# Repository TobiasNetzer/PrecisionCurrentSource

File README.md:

## A precision current source that can be configured for currents up to ~10mA.

I needed to verify the current measurement accuracy of the low-current ranges of my data logger and a reference for calibration purposes. Since I don’t own a programmable current source like a Keithley 220 or SMU, I came up with this approach instead. Check [here](https://tobiasnetzer.github.io/posts/current-source/) for more info.

Documentation
- [Schematic](https://github.com/TobiasNetzer/PrecisionCurrentSource/blob/main/Documentation/Schematic.pdf)
- [Assembly Drawing](https://github.com/TobiasNetzer/PrecisionCurrentSource/blob/main/Documentation/Assembly%20Drawing.pdf)
- [BOM](https://htmlpreview.github.io/?https://github.com/TobiasNetzer/PrecisionCurrentSource/blob/main/Documentation/BOM.html)

---

## Limitations of the Design

Due to the high internal resistance of CR2032 coin cells, they are unable to deliver currents higher than approximately 15mA. This inherently limits the maximum output of the constant current source. However, it's not the only limiting factor. The op-amp used in the circuit can only sink up to 15mA, making the current source only suitable for output currents up to around 10mA.  

In addition, the voltage swing across the load is limited to 1.4V. For example, at a current of 1mA, the maximum  load is limited to 1.4kΩ. This further restricts the usable range of the current source.

These limitations should be taken into account when using this current source!

## First Tests

The design has not been fully tested yet! The output current has been measured to be within ±0.2%.

| Configured Current &nbsp; &nbsp; &nbsp; &nbsp; &nbsp; &nbsp;          | Measured Current &nbsp; &nbsp; &nbsp; &nbsp; &nbsp; &nbsp;        | Error &nbsp; &nbsp; &nbsp; &nbsp; &nbsp; &nbsp;           |
| ---                                                                   | ---                                                               | ---                                                       |
| 100nA                                                                 | 99.82nA                                                           | -0.18%                                                    |
| 1µA                                                                   | 0.999µA                                                           | -0.1%                                                     |
| 100µA                                                                 | 100.07µA                                                          | 0.07%                                                     |
| 1mA                                                                   | 0.999mA                                                           | -0.1%                                                     |

Several other aspects such as load regulation, temperature stability and ripple/noise should also be tested. However, I currently lack the equipment to accurately perform these tests.

I did sample the output current with my datalogger at 1kHz to get an idea of how noisy the current source is. These results should be taken with a grain of salt, since the logger’s ADC does some internal averaging and I don't have a known reference to test the logger against.

| Current Source &nbsp; &nbsp; &nbsp; &nbsp; &nbsp; &nbsp;          | Peak-Peak Current &nbsp; &nbsp; &nbsp; &nbsp; &nbsp; &nbsp;     |
| ---                                                               | ---                                                             |
| 1µA                                                               | 1.23nA                                                          |
| 100µA                                                             | 73.25nA                                                         |
| 1mA                                                               | 1.24µA                                                          |

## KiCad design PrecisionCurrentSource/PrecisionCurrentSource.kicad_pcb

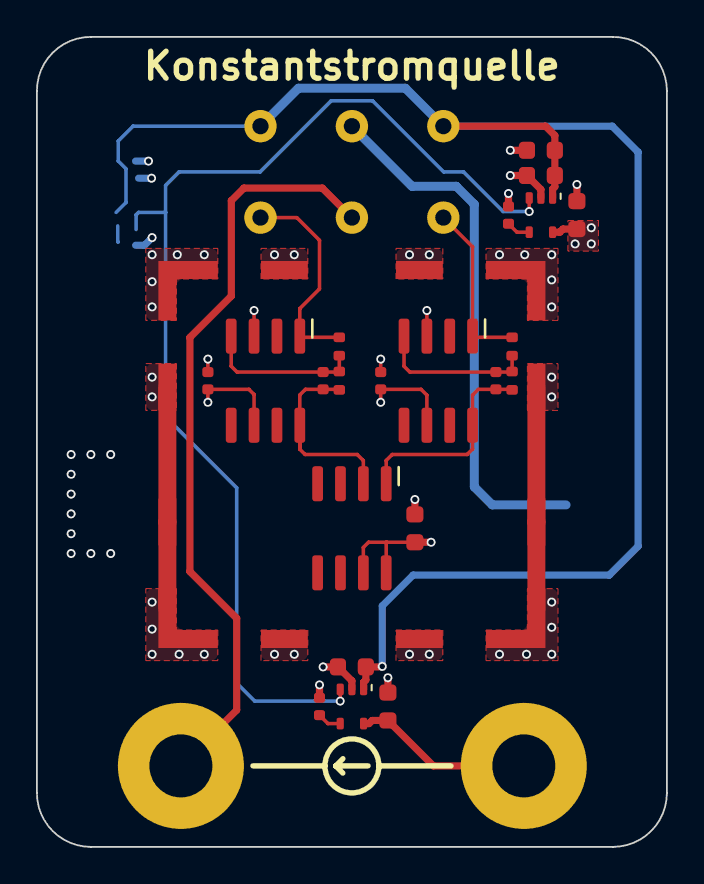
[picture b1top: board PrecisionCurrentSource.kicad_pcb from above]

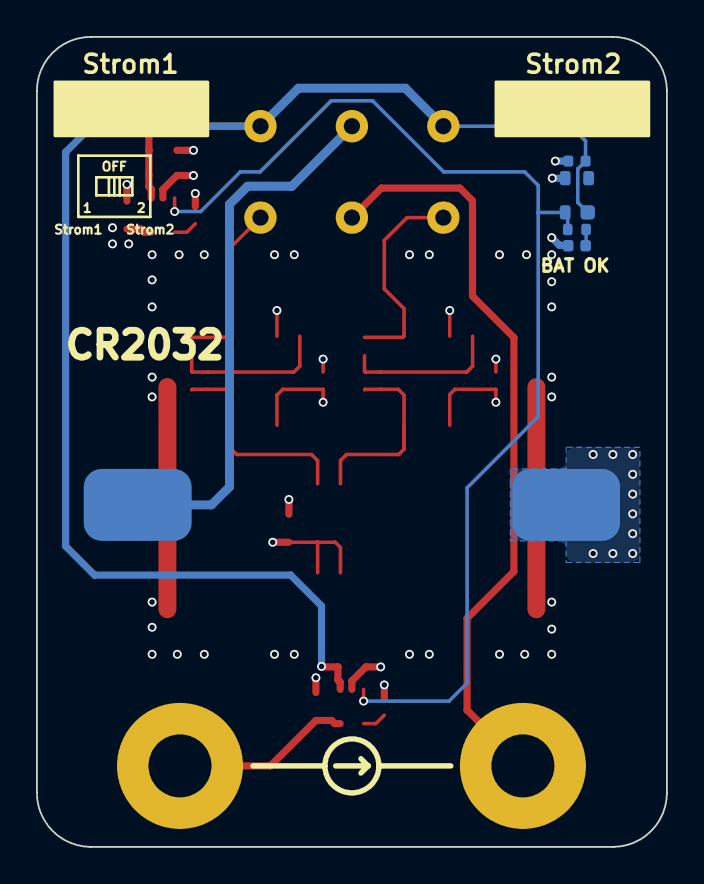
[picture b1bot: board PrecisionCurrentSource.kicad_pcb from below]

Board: 4 copper layers, 35.0 x 45.0 mm, 30 parts (6 on the bottom side), 16 nets.

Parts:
BT1: 2x CR2032; Keystone_1062
C1, C13: 10µF; Capacitor_0603
C2, C3, C5: 100nF; Capacitor_0402
C4, C6, C8, C11: 10nF; Capacitor_0402
C7, C9, C10, C12: 1µF; Capacitor_0603
D1: Green; LED_0402
H1, H2: MountingHole
J1: EMI-Shield; Wuerth_36103205_20x20mm
R1: 8k2; Resistor_0402
R2, R4: 1k 0,05%; Resistor_0402
R3: 1M 0,1%; Resistor_0402
R5: 100k 0,05%; Resistor_0402
SW1: 600DP3S2M4R
U1: BU4947F; SOP4
U2, U3: LMP7721; SOIC-8
U4: REF200AU; SOIC-8
U5: TPS71745; SC70-5
U6: TPS71715; SC70-5

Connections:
+1V5: C12.1, H1.1, U6.5 (OUT)
+4V5: C3.1, C5.1, C9.1, C13.1, U2.6 (V+), U3.6 (V+), U4.7, U4.8, U5.5 (OUT)
+BATT: C1.1, C2.1, C7.1, C10.1, SW1.4 (A), SW1.6 (C), U1.2 (VDD), U5.1 (IN), U6.1 (IN)
/PWR_EN: R1.1, U1.1 (VOUT), U5.3 (EN), U6.3 (EN)
GND: BT1.2 (-), C1.2, C2.2, C3.2, C5.2, C7.2, C8.2, C9.2, C10.2, C11.2, C12.2, C13.2, D1.1 (K), J1.1 (Shield), U1.4 (GND), U2.3 (V-), U3.3 (V-), U5.2 (GND), U6.2 (GND)
unnamed: BT1.1 (+), SW1.5 (B)
unnamed: C4.2, R2.2, R3.2, U2.4
unnamed: C6.2, R4.2, R5.2, U3.4
unnamed: D1.2 (A), R1.2
unnamed: R3.1, SW1.1 (A), U2.1 (+)
unnamed: H2.1, SW1.2 (B)
unnamed: R5.1, SW1.3 (C), U3.1 (+)
unnamed: C4.1, R2.1, U2.8 (-), U4.1
unnamed: C6.1, R4.1, U3.8 (-), U4.2
unnamed: C8.1, U5.4 (NR)
unnamed: C11.1, U6.4 (NR)

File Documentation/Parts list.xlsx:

Position | Menge | Reference(s) | Wert/Typ | Beschreibung | Hersteller | Hersteller-Nr. | Lieferant | Lieferant-Nr. | Stückpreis | Gesamtpreis
1 | 1 | BT1 | 2x CR2032 | Coin Cell Battery Holders 2X20MM SMT COIN HOLDER | Keystone Electronics | 1062 | Mouser | 534-1062 | 3.02 | 3.02
2 | 2 | C1, C13 | 10µF | 10µF-20%-0603-X5R-10V | Kemet | C0603C106M8PACTU | Mouser | 80-C0603C106M8PACTU | 0.43 | 0.86
3 | 3 | C2, C3, C5 | 100nF | 100nF-20%-0402-X7R-25V | Kemet | C0402C104M3RACTU | Mouser | 80-C0402C104M3R | 0.26 | 0.78
4 | 4 | C4, C6, C8, C11 | 10nF | 10nF-10%-0402-X7R-50V | Kemet | C0402C103K5REC7411 | Mouser | 80-C0402C103K5RECLR | 0.1 | 0.4
5 | 4 | C7, C9, C10, C12 | 1µF | 1µF-10%-0603-X7R-25V | Kemet | C0603C105K3RACTU | Mouser | 80-C0603C105K3R | 0.26 | 1.04
6 | 1 | D1 | Green | LED Green 0402 | Kingbright | APHHS1005ZGC | Mouser | 604-APHHS1005ZGC | 0.66 | 0.66
7 | 1 | J1 | EMI-Shield | EMI Gaskets, Sheets, Absorbers & Shielding WE-SHC SMD Frame 21x21mm | Würth Elektronik | 36103205 | Mouser | 710-36103205 | 2.9 | 2.9
8 | 1 | R1 | 8k2 | 8k2-1%-0402-62.5mW-100ppm | Yageo | AC0402FR-138K2L | Mouser | 603-AC0402FR-138K2L | 0.09 | 0.09
9 | 2 | R2, R4 | 1k 0,05% | 1k-0.05%-0402-62.5mW-5ppm | Susumu | RG1005V-102-W-T1 | Mouser | 754-RG1005V-102-WT1 | 3.12 | 6.24
10 | 1 | R3 | 1M 0,1% | 1M-0.1%-0402-100mW-25ppm | Vishay | MCS0402MD1004BE000 | Mouser | 594-MCS0402MD1004BE0 | 0.66 | 0.66
11 | 1 | R5 | 100k 0,05% | 100k-0.05%-0402-62.5mW-10ppm | Vishay | TNPU0402100KAYEP00 | Mouser | 71-TNPU0402100KAYEP0 | 1.56 | 1.56
12 | 1 | SW1 | 600DP3S2M4R | Schiebeschalter DPDT Durchkontaktierung | E-Switch | 600DP3S2M4R | Digikey | 600DP3S2M4R-ND | 2.29 | 2.29
13 | 1 | U1 | BU4947F | Supervisory Circuits IC CMOS VOLT DETECT | ROHM Semiconductor | BU4947F-TR | Mouser | 755-BU4947F-TR | 0.54 | 0.54
14 | 2 | U2, U3 | LMP7721 | Präzisionsverstärker 3 FEMTOAMPERE INPUT BIAS CURR PREC AMP | Texas Instruments | LMP7721MA/NOPB | Mouser | 926-LMP7721MA/NOPB | 6.12 | 12.24
15 | 1 | U4 | REF200AU | Strom- und Leistungswächter und -regler Dual Current Source Current Sink | Texas Instruments | REF200AU | Mouser | 595-REF200AU | 11.01 | 11.01
16 | 1 | U5 | TPS71745 | LDO Voltage Regulators AC SGL Out LDO 150mA Fixed High PSRR | Texas Instruments | TPS71745QDCKRQ1 | Mouser | 595-TPS71745QDCKRQ1 | 1.44 | 1.44
17 | 1 | U6 | TPS71715 | LDO Spannungs-Regulator LN High-BW PSRR 150mA | Texas Instruments | TPS71715DCKT | Mouser | 595-TPS71715DCKT | 1.46 | 1.46
 |  |  |  |  |  |  |  |  |  | 47.189999999999991

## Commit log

2025-04-26 upload src
2025-06-29 add docs
2025-08-10 update limitations
